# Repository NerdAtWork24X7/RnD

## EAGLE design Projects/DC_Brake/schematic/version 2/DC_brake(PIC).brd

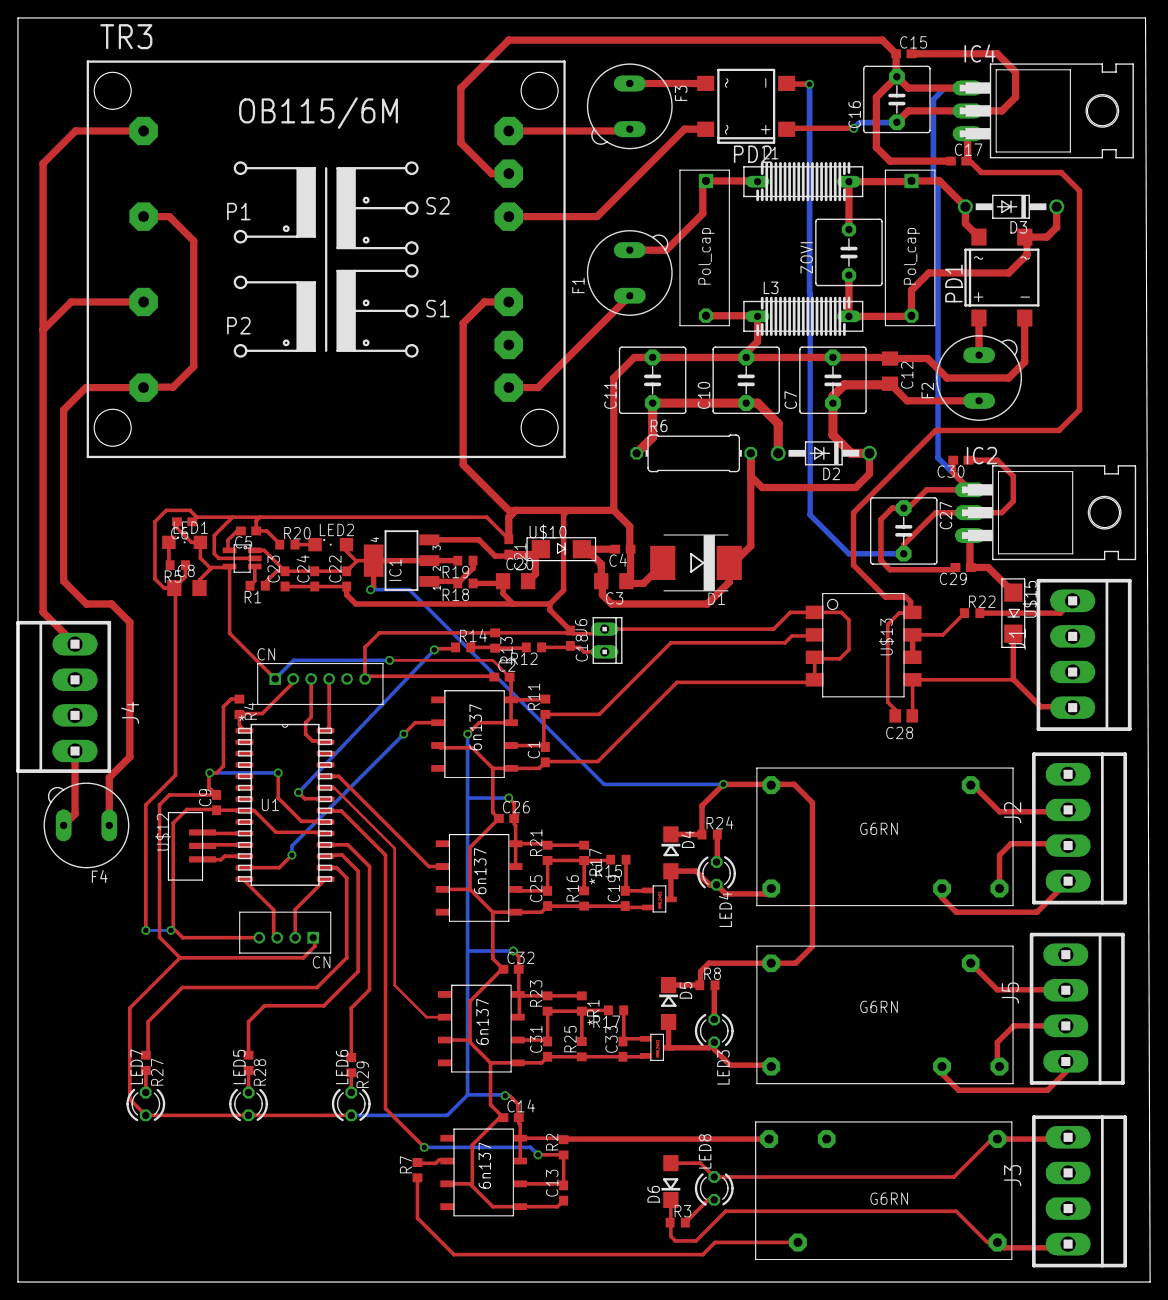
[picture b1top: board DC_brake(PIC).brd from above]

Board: 2 copper layers, 126.0 x 140.6 mm, 113 parts (0 on the bottom side), 71 nets.

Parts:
*R1, *R17: 100; R0603
C1, C13, C18, C19, C25, C31, C33: C0603
C2, C14, C26, C32: 0.1uF; C0603
C3, C8, C12: 10uF/16V; C1206
C4, C15, C30: 100nF MRa; C0603
C5: 1nF MRA; C0603
C6: 1uF/10V; C0603
C7: 4700uF/50V; C050-075X075
C9: 100nF/10V; C0603
C10, C11, C16, C27: 4700uF/50v; C050-075X075
C17, C29: 10mF MRa; C0603
C20: 1uF/50V; C1206
C21: 100nF/50V; C0603
C22: 100nF; C0603
C23: 1uF; C0603
C24: 10nF; C0603
C28: C0805
D1: 18V; SMC
D2: 1N4004; DO41-10
D3: DO41-10
D4, D5, D6: DO214AC
F1, F2, F3, F4: 19560
IC1: 317EMP; SOT223
IC2: lm7905; TO220H
IC4: lm7812; TO220H
J1, J2, J3, J4, J5: 1X4MTA
J6: 10X02MTA
L1, L3: DS10
LED1, LED2: SML1206
LED3, LED4, LED5, LED6, LED7, LED8: LED3MM
PD1, PD2: DF01S; DBS
R1, R5, R20: 10K; R0603
R2, R3, R7, R8, R11, R12, R13, R14, R15, R16, R17, R21, R22, R23, R24, R25, R27, R28, R29: 100; R0603
R4: 300; R0603
R6: 0411/12
R18: 2K; R0603
R19: 470R; R0603
T1, T2: IRML2402
TR3: OB115/6M
U1: PIC16F886-X/SO; SOIC28-W_MC
U$1: MIC5205-5.YMS; SMD
U$2, U$3, U$11, U$14: 6N137
U$4: 6PIN
U$5, U$9, U$16: RELAY
U$6: 4PIN
U$7, U$8: POLY_CAP; POL_CAP
U$10, U$15: DIODE
U$12: 3PIN
U$13: HCPL-3120
ZOVI: C5B7.2

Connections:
+12V: C17.2, C28.2, IC4.3, U$13.8(VCC)
-5V: C28.1, J1.1, U$13.5(VEE), U$15.-
CONTACT_RELAY: U1.24, U$11.2
D_GND: C15.1, C16.2, C17.1, C27.1, C29.2, C30.2, IC2.1, IC4.1, TR3.9
ES1: U1.12, U$12.3
ES2: U1.10, U$12.1
ES_COM: U1.11, U$12.2
GND: C1.1, C2.1, C3.1, C4.1, C5.1, C6.1, C7.2, C8.1, C9.1, C10.2, C11.2, C12.1, C13.1, C14.1, C18.1, C19.1, C20.1, C21.1, C22.1, C23.1, C24.1, C25.1, C26.1, C31.1, C32.1, C33.1, D1.A, J6.2, L3.1, PD1.-, R5.1, R13.1, R16.1, R18.1, R20.1, R25.1, T1.2, T2.2, TR3.7, U1.8, U1.19, U$1.2, U$2.3, U$2.5, U$3.3, U$3.5, U$4.6, U$6.4, U$7.2, U$11.3, U$11.5, U$13.1(N/C), U$13.3(CA), U$13.4(N/C), U$14.3, U$14.5
I2C_SCL: U1.14, U$6.3
I2C_SDA: U1.15, U$6.2
IGBT_TRIG: U1.13, U$3.2
LED1: R27.1, U1.16
LED2: R28.1, U1.17
LED3: R29.1, U1.18
unnamed: C29.1, IC2.3, U$15.+
unnamed: C5.2, U$1.4
unnamed: F1.2, L1.1, U$7.1
unnamed: R1.2, U$1.3
unnamed: F4.1, TR3.2, TR3.4
unnamed: F1.1, TR3.5
unnamed: J4.1, TR3.1, TR3.3
unnamed: F4.2, J4.4
unnamed: J1.4, R22.2
unnamed: C10.1, C11.1, D2.A, R6.1
unnamed: F3.2, TR3.10
unnamed: J2.1, U$9.NC
unnamed: C3.2, C4.2, C7.1, C12.2, D1.C, D2.C, F2.1, R6.2, U$10.-
unnamed: LED1.C, R5.2
unnamed: D6.A, J3.4, LED8.K, U$5.C2
unnamed: LED8.A, R3.2
unnamed: R7.2, U$2.2
unnamed: R7.1, U$5.COM
unnamed: D6.C, J3.1, R3.1, U$5.C1
unnamed: D5.A, LED3.K, T2.3, U$16.C2
unnamed: LED3.A, R8.2
unnamed: J5.1, U$16.NC
unnamed: J5.2, U$16.NO
unnamed: J5.3, U$16.COM
unnamed: PD2.AC1, TR3.8
unnamed: D3.A, L1.2, PD1.AC1, U$8.1, ZOVI.2
unnamed: D3.C, L3.2, PD1.AC2, U$8.2, ZOVI.1
unnamed: F3.1, PD2.AC2
unnamed: J2.2, U$9.NO
unnamed: C1.2, R11.1, U$3.6, U$13.2(AN)
unnamed: C15.2, C16.1, IC4.2, PD2.+
unnamed: C18.2, J6.1, R12.1
unnamed: J2.3, U$9.COM
unnamed: F2.2, PD1.+
unnamed: R12.2, R13.2, R14.2
unnamed: C19.2, R15.1, T1.1
unnamed: D4.A, LED4.K, T1.3, U$9.C2
unnamed: C33.2, R17.1, T2.1
unnamed: *R17.2, C25.2, R15.2, R16.2, R21.1, U$11.6
unnamed: LED2.C, R20.2
unnamed: IC1.1, R18.2, R19.1
unnamed: C20.2, C21.2, IC1.3, U$10.+
unnamed: C27.2, C30.1, IC2.2, PD2.-
unnamed: R22.1, U$13.6(VO), U$13.7(VO)
unnamed: *R1.2, C31.2, R17.2, R23.1, R25.2, U$14.6
unnamed: LED4.A, R24.2
unnamed: LED7.K, R27.2
unnamed: LED5.K, R28.2
unnamed: LED6.K, R29.2
RST: R4.2, U1.1, U$4.2
RX: U1.28, U$4.4
SER_RES_RELAY: U1.23, U$14.2
S_CMD: C13.2, R2.1, U1.21, U$2.6
TEMP: R14.1, U1.22
TX: U1.27, U$4.3
VCC: *R1.1, *R17.1, C2.2, C6.2, C8.2, C9.2, C14.2, C26.2, C32.2, LED1.A, LED5.A, LED6.A, LED7.A, R2.2, R4.1, R11.2, R21.2, R23.2, U1.20, U$1.5, U$2.7, U$2.8, U$3.7, U$3.8, U$4.1, U$5.NO, U$6.1, U$11.7, U$11.8, U$14.7, U$14.8
VDD: C22.2, C23.2, C24.2, D4.C, D5.C, IC1.4, LED2.A, R1.1, R8.1, R19.2, R24.1, U$1.1, U$9.C1, U$16.C1

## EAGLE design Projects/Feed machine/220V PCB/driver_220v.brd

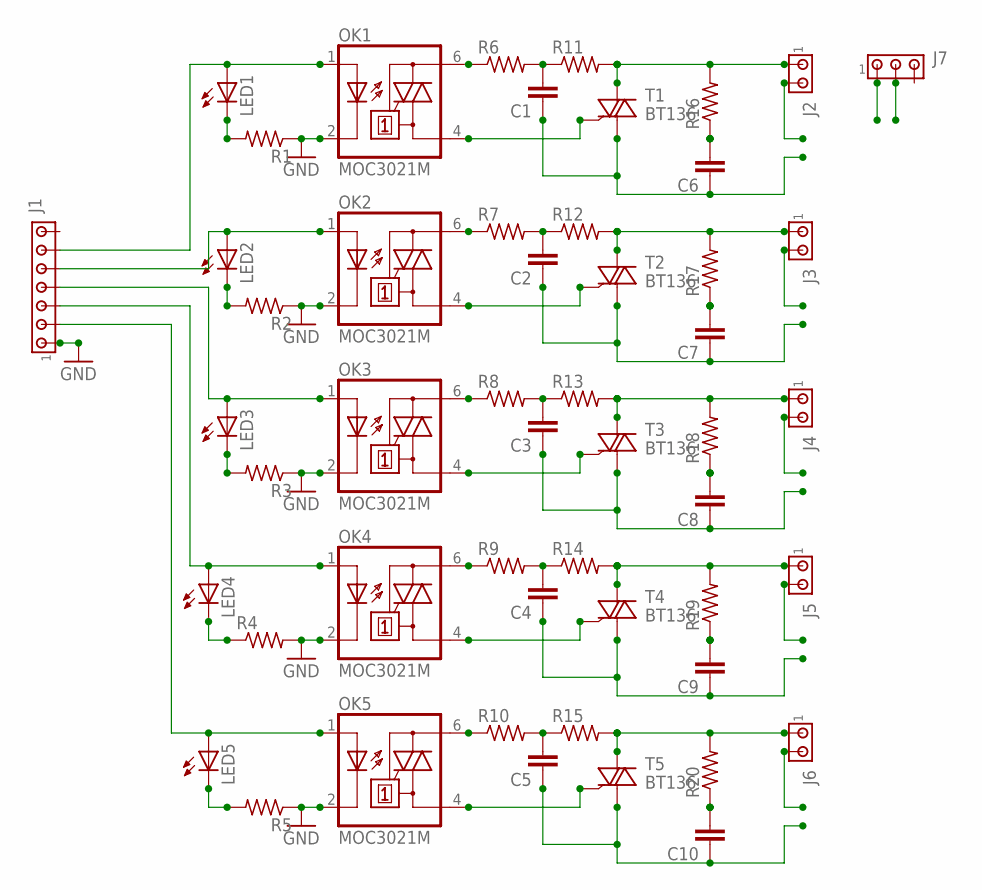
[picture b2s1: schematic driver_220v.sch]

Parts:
C1, C2, C3, C4, C5, C6, C7, C8, C9, C10: C2,5-3; C2.5-3
J1: MTA07-100; 10X07MTA
J2, J3, J4, J5, J6: MTA02-156; 1X2MTA
J7: MTA03-156; 1X3MTA
LED1, LED2, LED3, LED4, LED5: LED5MM
OK1, OK2, OK3, OK4, OK5: MOC3021M; DIL06
R1, R2, R3, R4, R5: R-US_R0603; R0603
R6, R7, R8, R9, R10, R11, R12, R13, R14, R15, R16, R17, R18, R19, R20: R-US_0207/10; 0207/10
T1, T2, T3, T4, T5: BT136; TO220AB

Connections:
GND: J1.1, OK1.2 (C), OK2.2 (C), OK3.2 (C), OK4.2 (C), OK5.2 (C), R1.1, R2.1, R3.1, R4.2, R5.1
LIVE: J2.2, J3.2, J4.2, J5.2, J6.2, J7.1
unnamed: OK2.6 (A2), R7.1
unnamed: C2.2, R7.2, R12.1
unnamed: J3.1, R12.2, R17.2, T2.2 (A2)
unnamed: OK2.4 (A1), T2.3 (G)
unnamed: C7.2, R17.1
unnamed: OK3.6 (A2), R8.1
unnamed: C3.2, R8.2, R13.1
unnamed: J4.1, R13.2, R18.2, T3.2 (A2)
unnamed: OK3.4 (A1), T3.3 (G)
unnamed: C8.2, R18.1
unnamed: OK4.6 (A2), R9.1
unnamed: C4.2, R9.2, R14.1
unnamed: J5.1, R14.2, R19.2, T4.2 (A2)
unnamed: OK4.4 (A1), T4.3 (G)
unnamed: C9.2, R19.1
unnamed: OK5.6 (A2), R10.1
unnamed: C5.2, R10.2, R15.1
unnamed: J6.1, R15.2, R20.2, T5.2 (A2)
unnamed: OK5.4 (A1), T5.3 (G)
unnamed: C10.2, R20.1
unnamed: J1.6, LED1.A, OK1.1 (A)
unnamed: J1.5, LED2.A, OK2.1 (A)
unnamed: OK1.6 (A2), R6.1
unnamed: C1.2, R6.2, R11.1
unnamed: J2.1, R11.2, R16.2, T1.2 (A2)
unnamed: OK1.4 (A1), T1.3 (G)
unnamed: J1.4, LED3.A, OK3.1 (A)
unnamed: C6.2, R16.1
unnamed: J1.3, LED4.A, OK4.1 (A)
unnamed: J1.2, LED5.A, OK5.1 (A)
unnamed: LED5.K (C), R5.2
unnamed: LED4.K (C), R4.1
unnamed: LED3.K (C), R3.2
unnamed: LED2.K (C), R2.2
unnamed: LED1.K (C), R1.2
NEUTRAL: C1.1, C2.1, C3.1, C4.1, C5.1, C6.1, C7.1, C8.1, C9.1, C10.1, J7.2, T1.1 (A1), T2.1 (A1), T3.1 (A1), T4.1 (A1), T5.1 (A1)

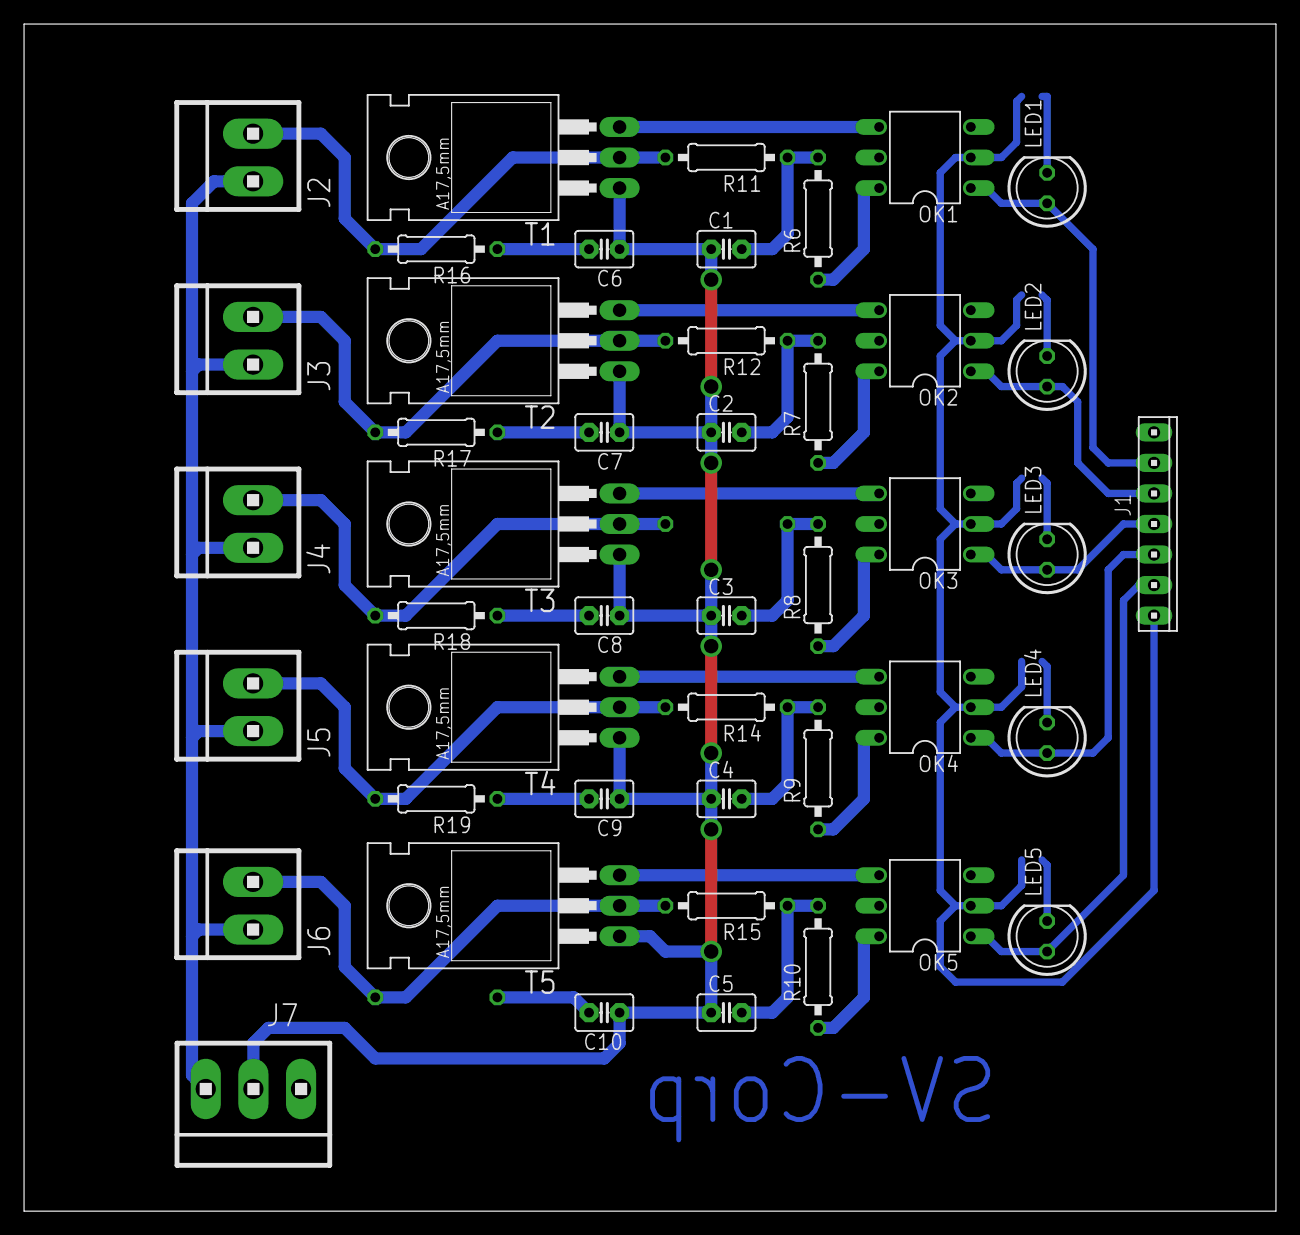
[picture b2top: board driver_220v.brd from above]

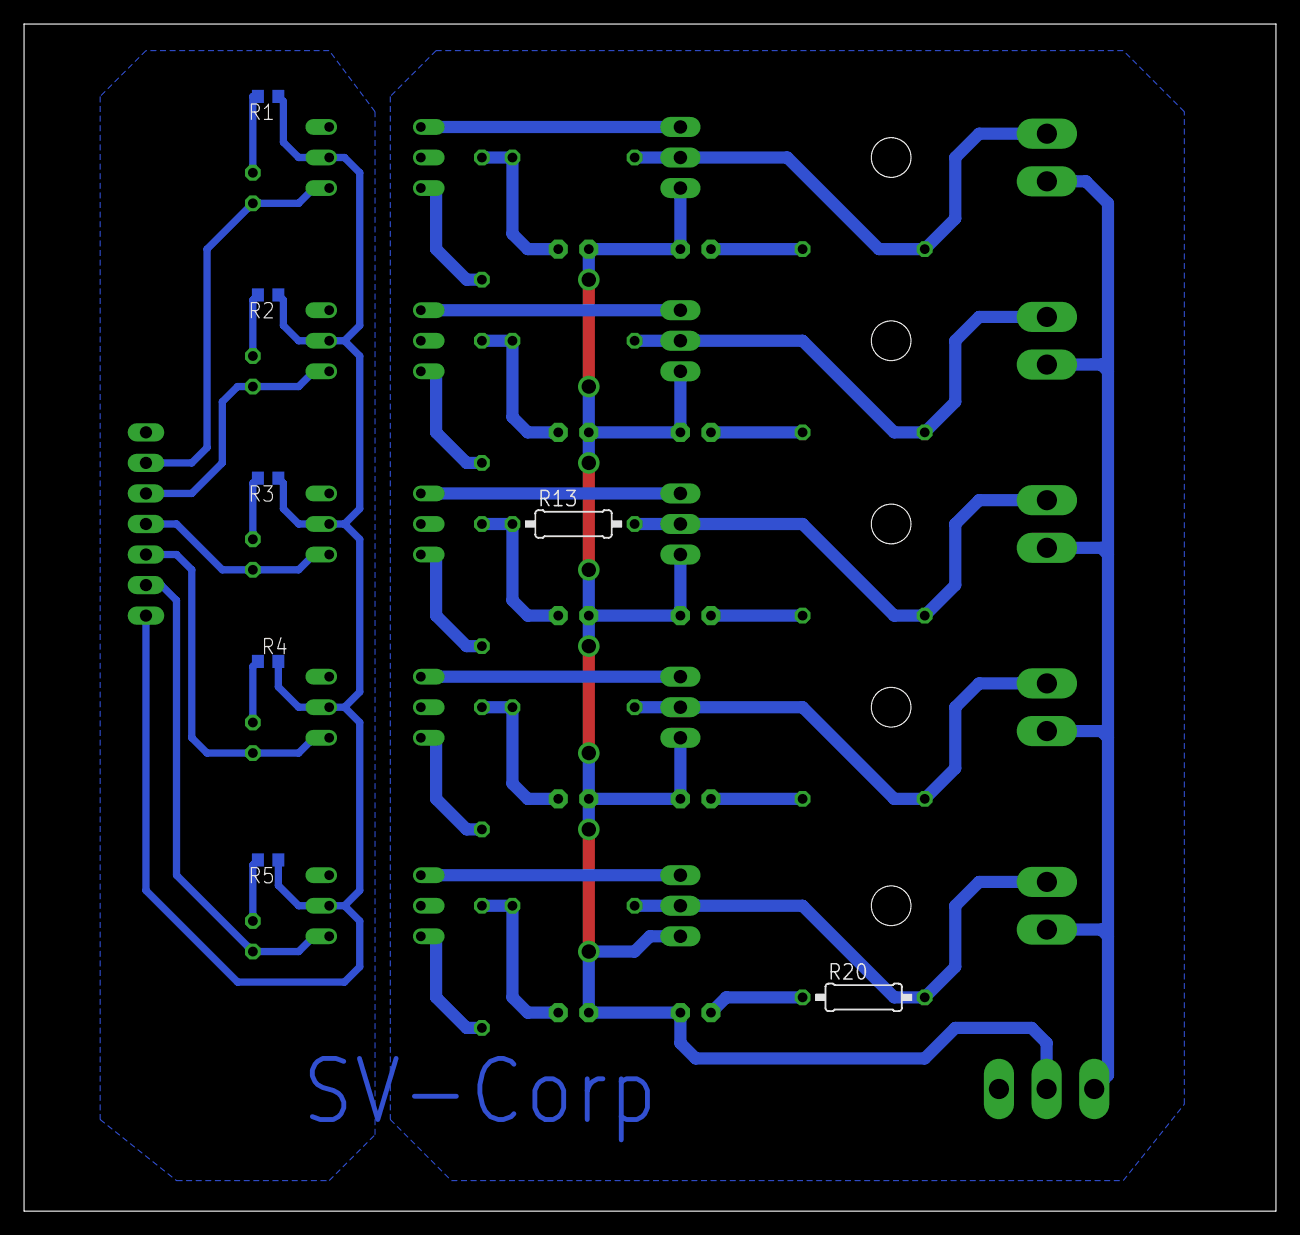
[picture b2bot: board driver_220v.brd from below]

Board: 2 copper layers, 104.1 x 98.7 mm, 52 parts (7 on the bottom side), 38 nets.

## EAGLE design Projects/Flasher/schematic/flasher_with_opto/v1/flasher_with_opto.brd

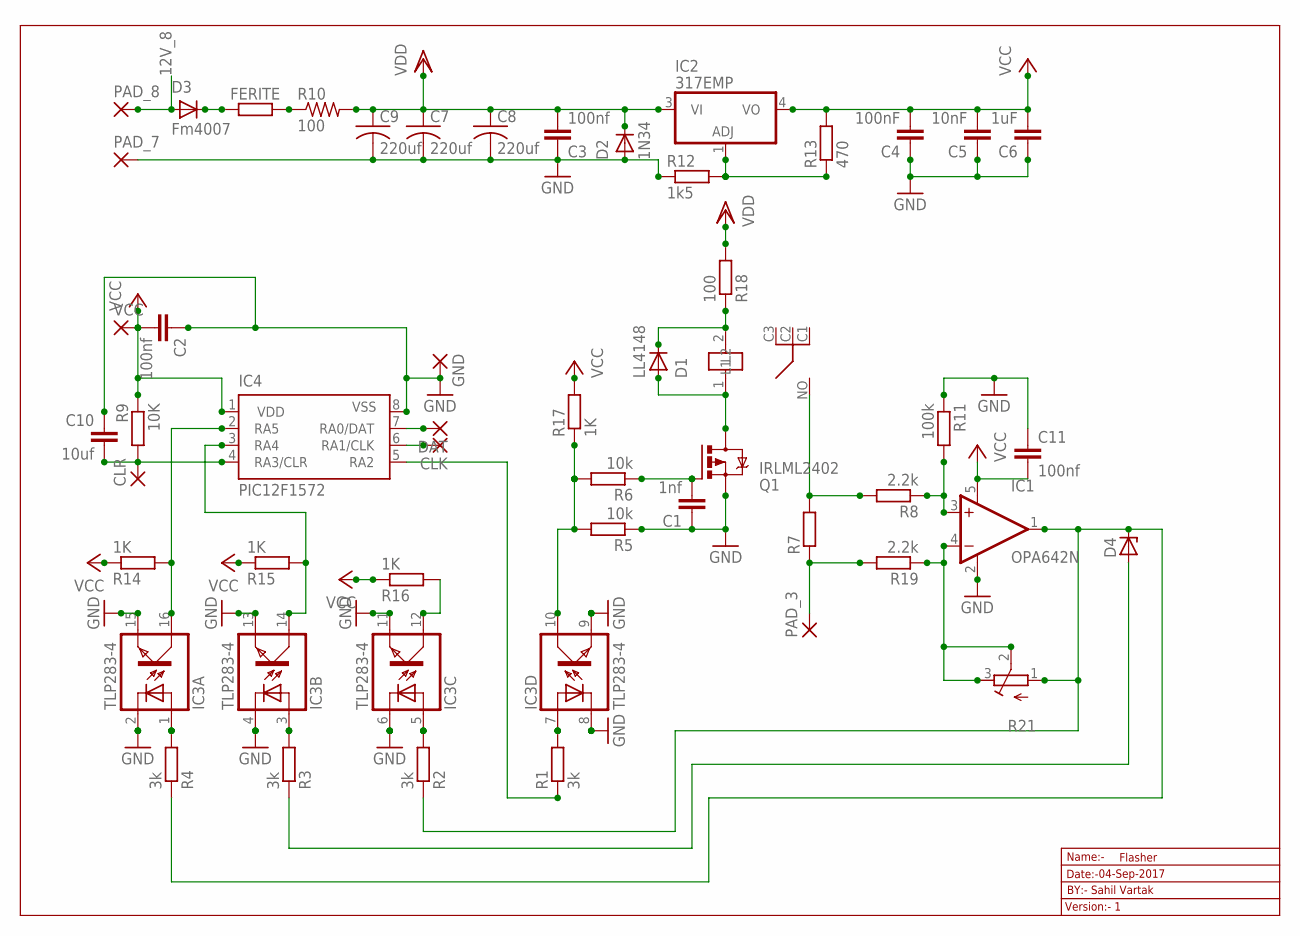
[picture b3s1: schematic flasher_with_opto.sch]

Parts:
C1: 1nf; C0603
C2, C3, C11: 100nf; C0603
C4: 100nF; C0603
C5: 10nF; C0603
C6: 1uF; C0603
C7, C8, C9: 220uf; C025-025X050
C10: 10uf; C0603
CLK: 1,6/0,8
CLR: 1,6/0,8
D1: LL4148; SMA-DO214AC
D2: 1N34; SMA-DO214AC
D3: Fm4007; SMA-DO214AC
D4: ZENER-DIODESOD80C; SOD80C
DAT: 1,6/0,8
FERITE: R-EU_R0603; R0603
GND: 1,6/0,8
IC1: OPA642N; SOT23-5
IC2: 317EMP; SOT223
IC3: TLP283-4; MINI-FLAT-16
IC4: PIC12F1572; SO-08
K2: RL703
PAD_3, PAD_7, PAD_8: 2,54/1,1
Q1: IRLML2402; MICRO3
R1, R2, R3, R4: 3k; R0603
R5, R6: 10k; R0603
R7: R-EU_VTA54; VTA54
R8, R19: 2.2k; R0603
R9: 10K; R0603
R10: 100; WSC2515
R11: 100k; R0603
R12: 1k5; R0603
R13: 470; R0603
R14, R15, R16, R17: 1K; R0603
R18: 100; R0603
R21: R-TRIMMTS63X; RTRIMTS63X
VCC: 1,6/0,8

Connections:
12V_8: D3.A, PAD_8.1
GND: C1.1, C2.1, C3.1, C4.1, C5.1, C6.1, C7.2, C8.2, C9.2, C10.1, C11.1, D2.A, GND.1, IC1.2 (V-), IC3.2 (C), IC3.4 (C), IC3.6 (C), IC3.8 (C), IC3.9 (EMIT), IC3.11 (EMIT), IC3.13 (EMIT), IC3.15 (EMIT), IC4.8 (VSS), PAD_7.1, Q1.2 (S), R5.1, R11.1, R12.1
unnamed: IC3.10 (COL), R5.2, R6.2, R17.1
unnamed: D1.A, K2.1 (L2), Q1.3 (D)
unnamed: D3.K (C), FERITE.1
unnamed: DAT.1, IC4.7 (RA0/DAT)
unnamed: CLK.1, IC4.6 (RA1/CLK)
unnamed: D1.K (C), K2.2 (L1), R18.1
unnamed: IC2.1 (ADJ), R12.2, R13.1
unnamed: FERITE.2, R10.1
unnamed: K2.NO, R7.2, R8.2
unnamed: IC3.12 (COL), R16.2
unnamed: IC4.5 (RA2), R1.1
unnamed: PAD_3.1, R7.1, R19.2
unnamed: IC3.14 (COL), IC4.3 (RA4), R15.2
unnamed: IC1.4 (-IN), R19.1, R21.2 (S), R21.3 (E)
unnamed: IC1.3 (+IN), R8.1, R11.2
unnamed: D4.C, IC1.1 (OUT), R2.1, R4.1, R21.1 (A)
unnamed: D4.A, R3.1
unnamed: C1.2, Q1.1 (G), R6.1
unnamed: IC3.1 (A), R4.2
unnamed: IC3.3 (A), R3.2
unnamed: IC3.5 (A), R2.2
unnamed: IC3.7 (A), R1.2
unnamed: IC3.16 (COL), IC4.2 (RA5), R14.2
unnamed: C10.2, CLR.1, IC4.4 (RA3/CLR), R9.2
VCC: C2.2, C4.2, C5.2, C6.2, C11.2, IC1.5 (V+), IC2.4 (VO), IC4.1 (VDD), R9.1, R13.2, R14.1, R15.1, R16.1, R17.2, VCC.1
VDD: C3.2, C7.1, C8.1, C9.1, D2.K (C), IC2.3 (VI), R10.2, R18.2

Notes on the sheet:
Name:-
Version:- 1
Date:-
Flasher
BY:- Sahil Vartak
04-Sep-2017

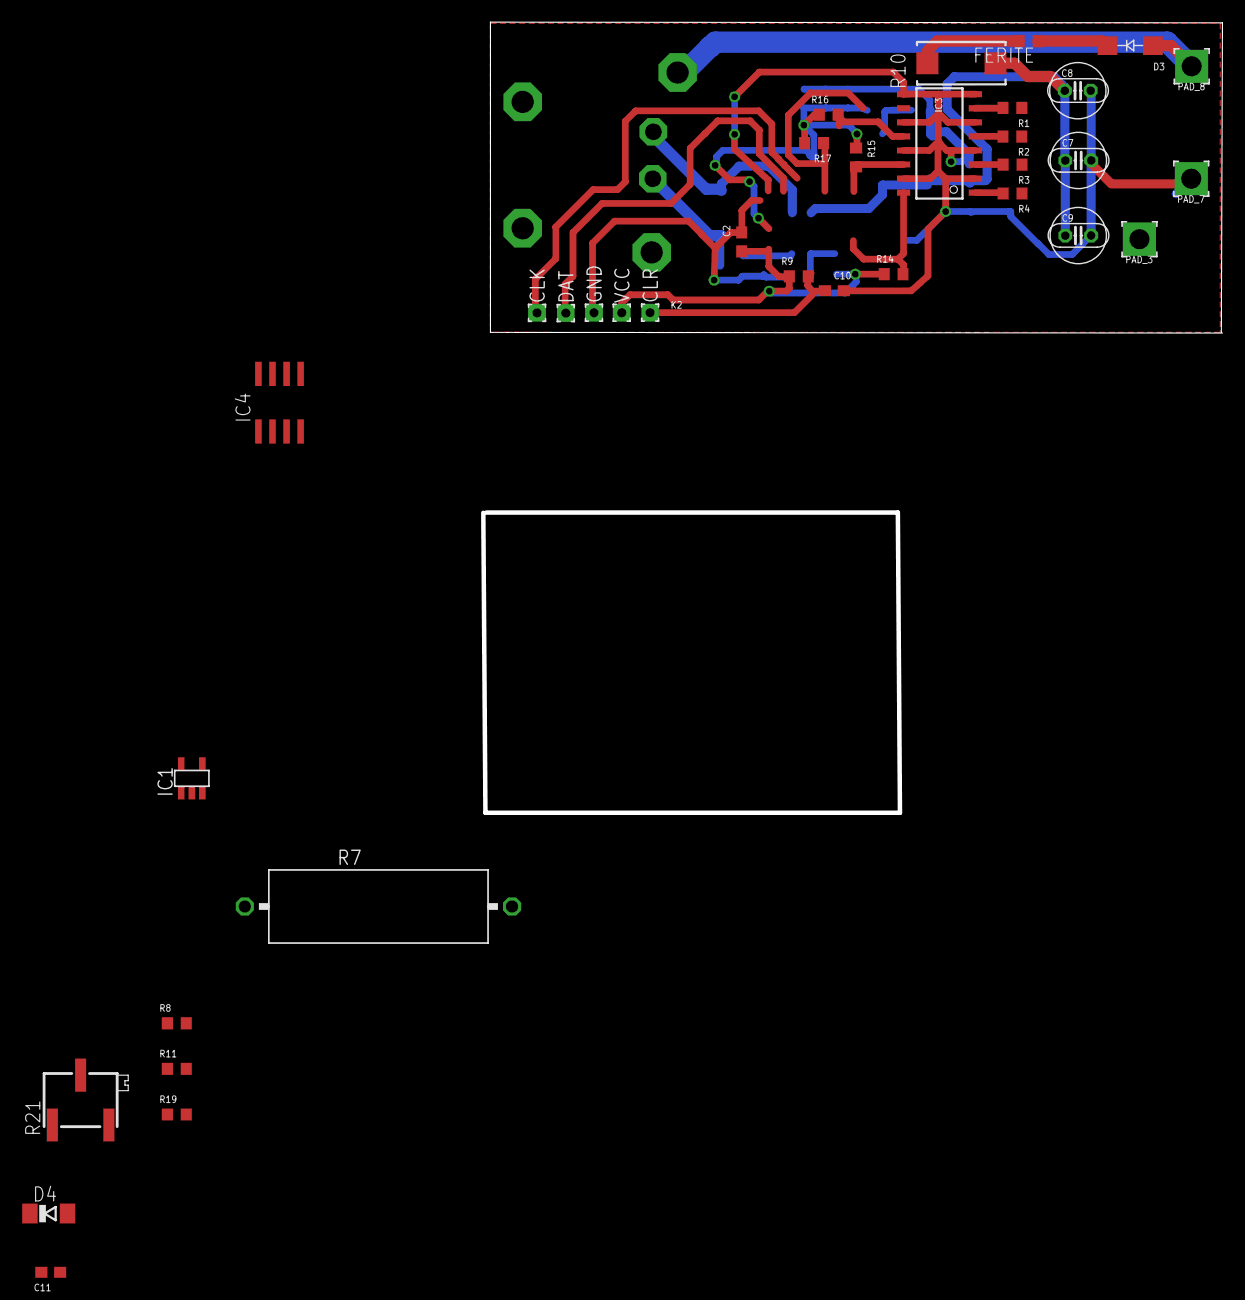
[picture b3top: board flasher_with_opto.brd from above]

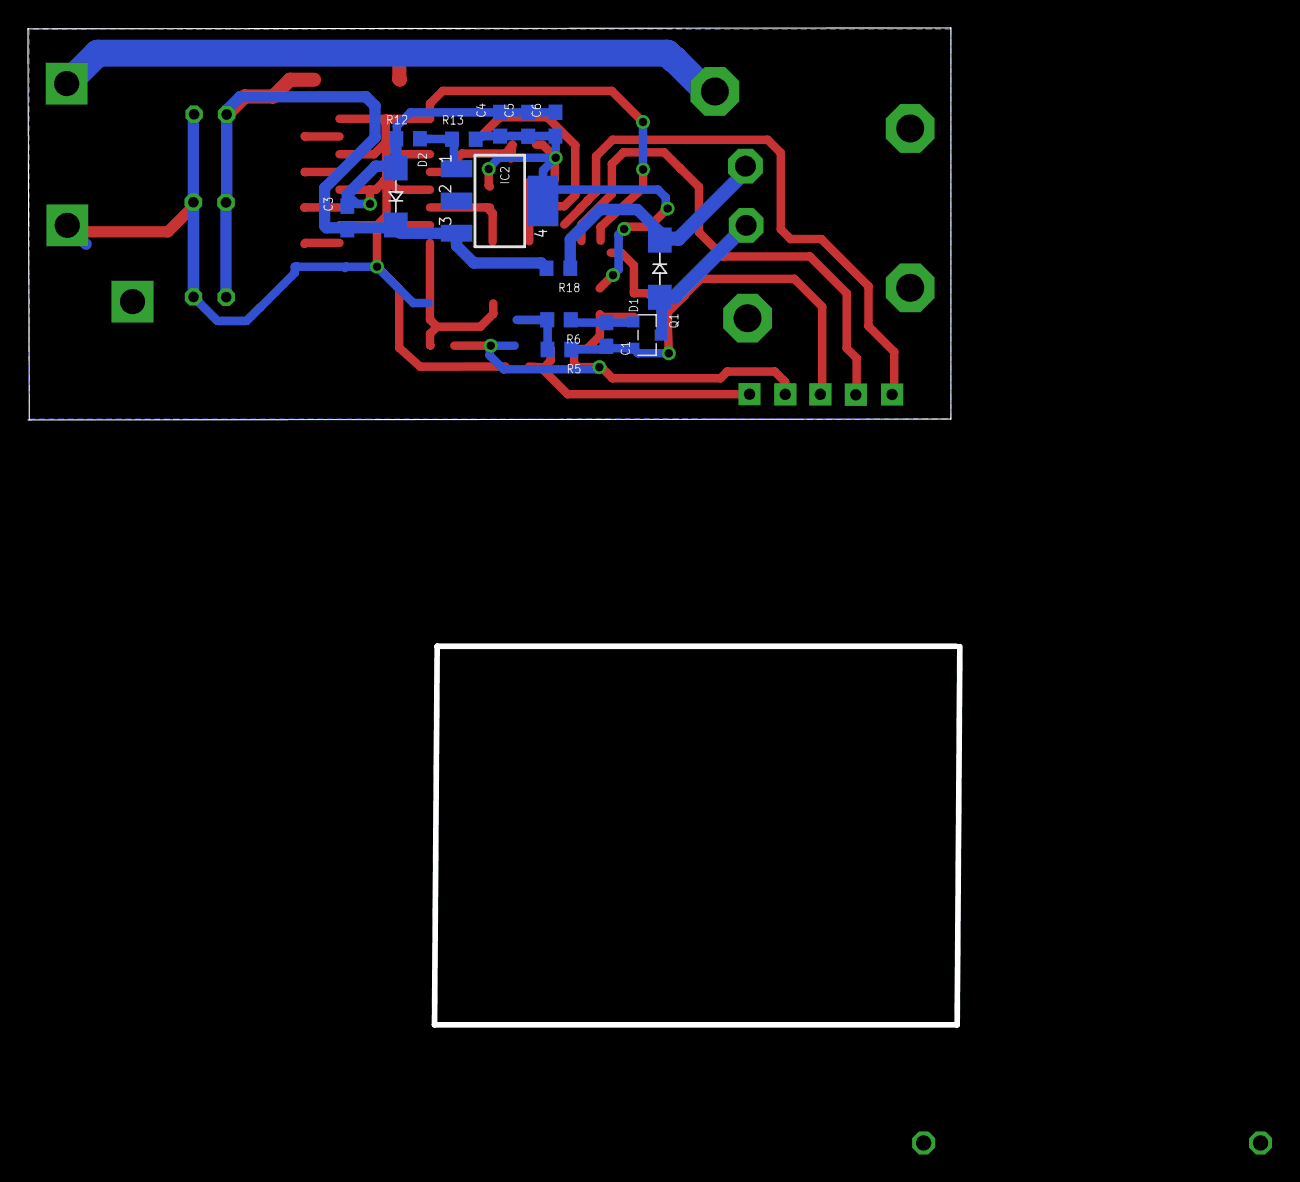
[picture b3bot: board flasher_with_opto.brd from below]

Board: 2 copper layers, 66.1 x 28.1 mm, 50 parts (15 on the bottom side), 28 nets.

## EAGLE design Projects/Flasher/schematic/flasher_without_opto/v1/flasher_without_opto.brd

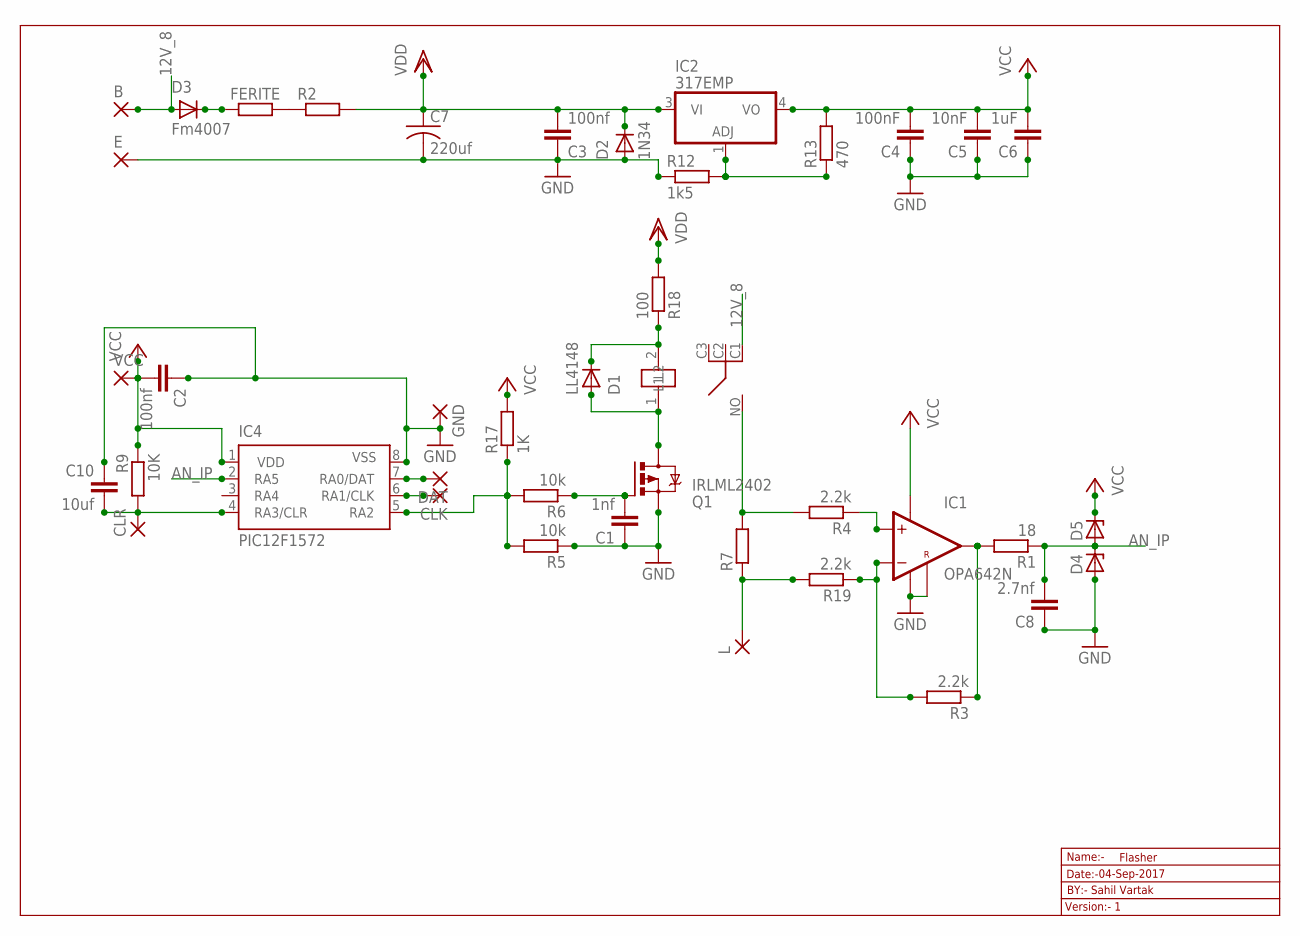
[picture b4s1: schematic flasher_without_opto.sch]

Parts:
B: 2,54/1,1
C1: 1nf; C0603
C2, C3: 100nf; C0603
C4: 100nF; C0603
C5: 10nF; C0603
C6: 1uF; C0603
C7: 220uf; C025-025X050
C8: 2.7nf; C0603
C10: 10uf; C0603
CLK: 1,6/0,8
CLR: 1,6/0,8
D1: LL4148; SMA-DO214AC
D2: 1N34; SMA-DO214AC
D3: Fm4007; SMA-DO214AC
D4, D5: ZENER-DIODESOD80C; SOD80C
DAT: 1,6/0,8
E: 2,54/1,1
FERITE: R-EU_R0603; R0603
GND: 1,6/0,8
IC1: OPA642N; INA181
IC2: 317EMP; SOT223
IC4: PIC12F1572; SO-08
K2: RL703
L: 2,54/1,1
Q1: IRLML2402; MICRO3
R1: 18; R0603
R2: RR5025; R5025
R3, R4, R19: 2.2k; R0603
R5, R6: 10k; R0603
R7: R-EU_0207/15; 0207/15
R9: 10K; R0603
R12: 1k5; R0603
R13: 470; R0603
R17: 1K; R0603
R18: 100; R0603
VCC: 1,6/0,8

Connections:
12V_8: B.1, D3.A, K2.C1
AN_IP: C8.2, D4.C, D5.A, IC4.2 (RA5), R1.1
GND: C1.1, C2.1, C3.1, C4.1, C5.1, C6.1, C7.2, C8.1, C10.1, D2.A, D4.A, E.1, GND.1, IC1.P$2 (V-), IC1.P$5 (REF), IC4.8 (VSS), Q1.2 (S), R5.1, R12.1
unnamed: FERITE.2, R2.1
unnamed: IC4.5 (RA2), R5.2, R6.2, R17.1
unnamed: D1.A, K2.1 (L2), Q1.3 (D)
unnamed: D3.K (C), FERITE.1
unnamed: DAT.1, IC4.7 (RA0/DAT)
unnamed: CLK.1, IC4.6 (RA1/CLK)
unnamed: D1.K (C), K2.2 (L1), R18.1
unnamed: IC2.1 (ADJ), R12.2, R13.1
unnamed: K2.NO, R4.2, R7.2
unnamed: L.1, R7.1, R19.2
unnamed: IC1.P$4 (-IN), R3.2, R19.1
unnamed: IC1.P$3 (+IN), R4.1
unnamed: IC1.P$1 (OUT), R1.2, R3.1
unnamed: C1.2, Q1.1 (G), R6.1
unnamed: C10.2, CLR.1, IC4.4 (RA3/CLR), R9.2
VCC: C2.2, C4.2, C5.2, C6.2, D5.C, IC1.P$6 (V+), IC2.4 (VO), IC4.1 (VDD), R9.1, R13.2, R17.2, VCC.1
VDD: C3.2, C7.1, D2.K (C), IC2.3 (VI), R2.2, R18.2

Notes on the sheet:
Name:-
Version:- 1
Date:-
Flasher
BY:- Sahil Vartak
04-Sep-2017

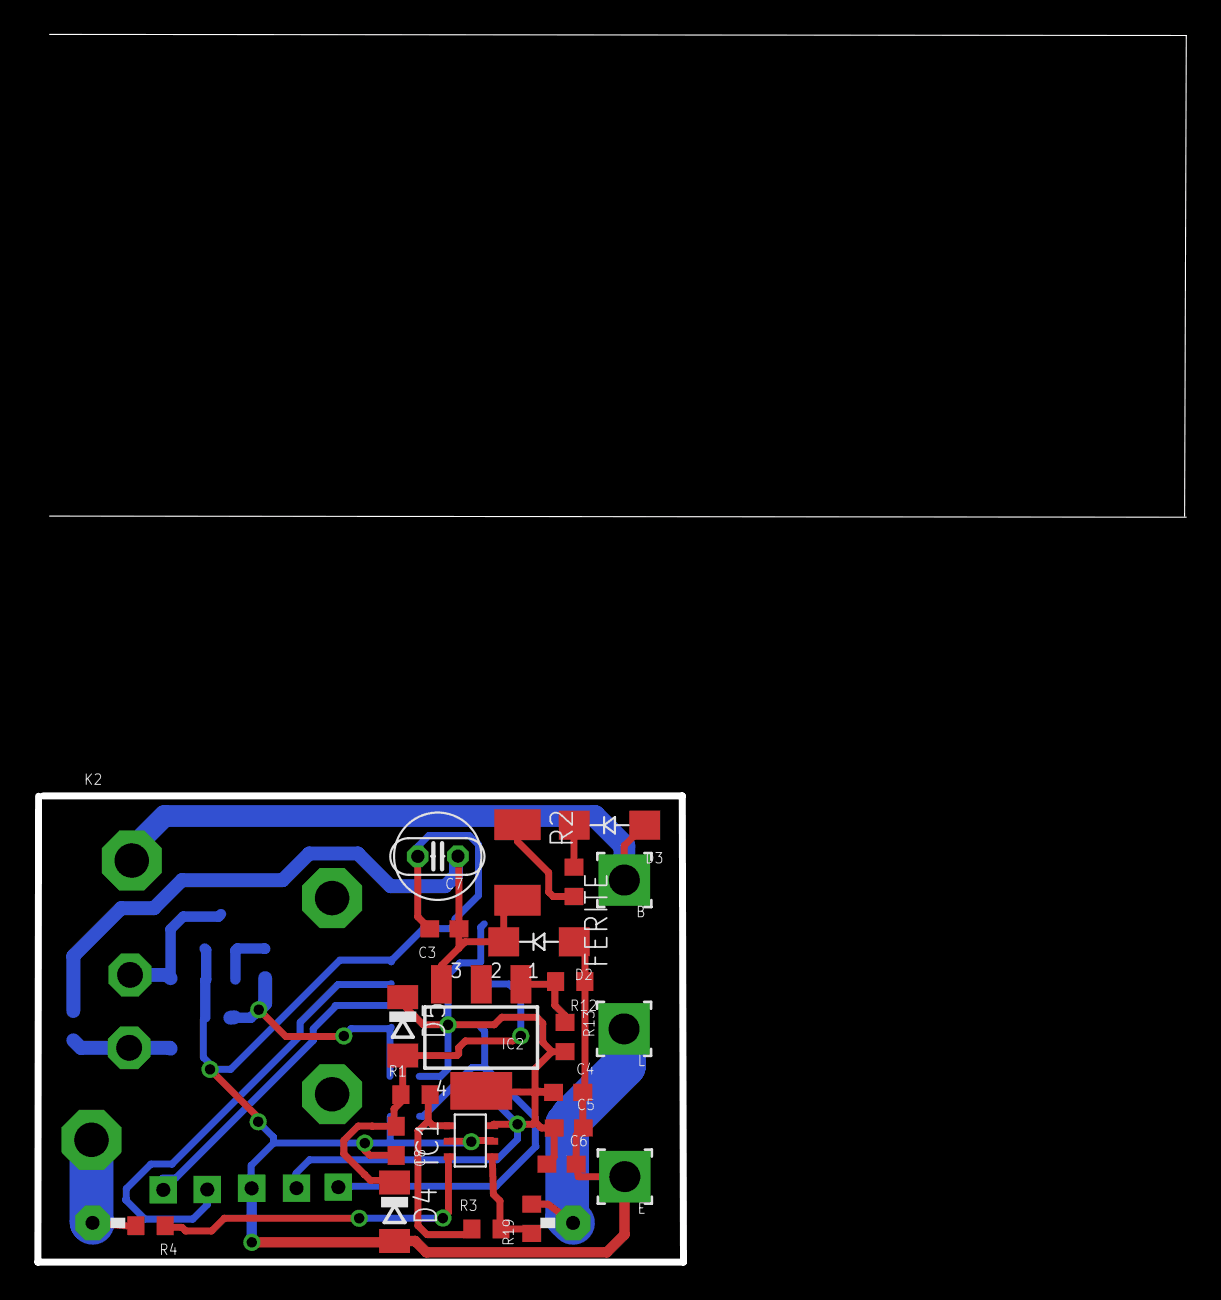
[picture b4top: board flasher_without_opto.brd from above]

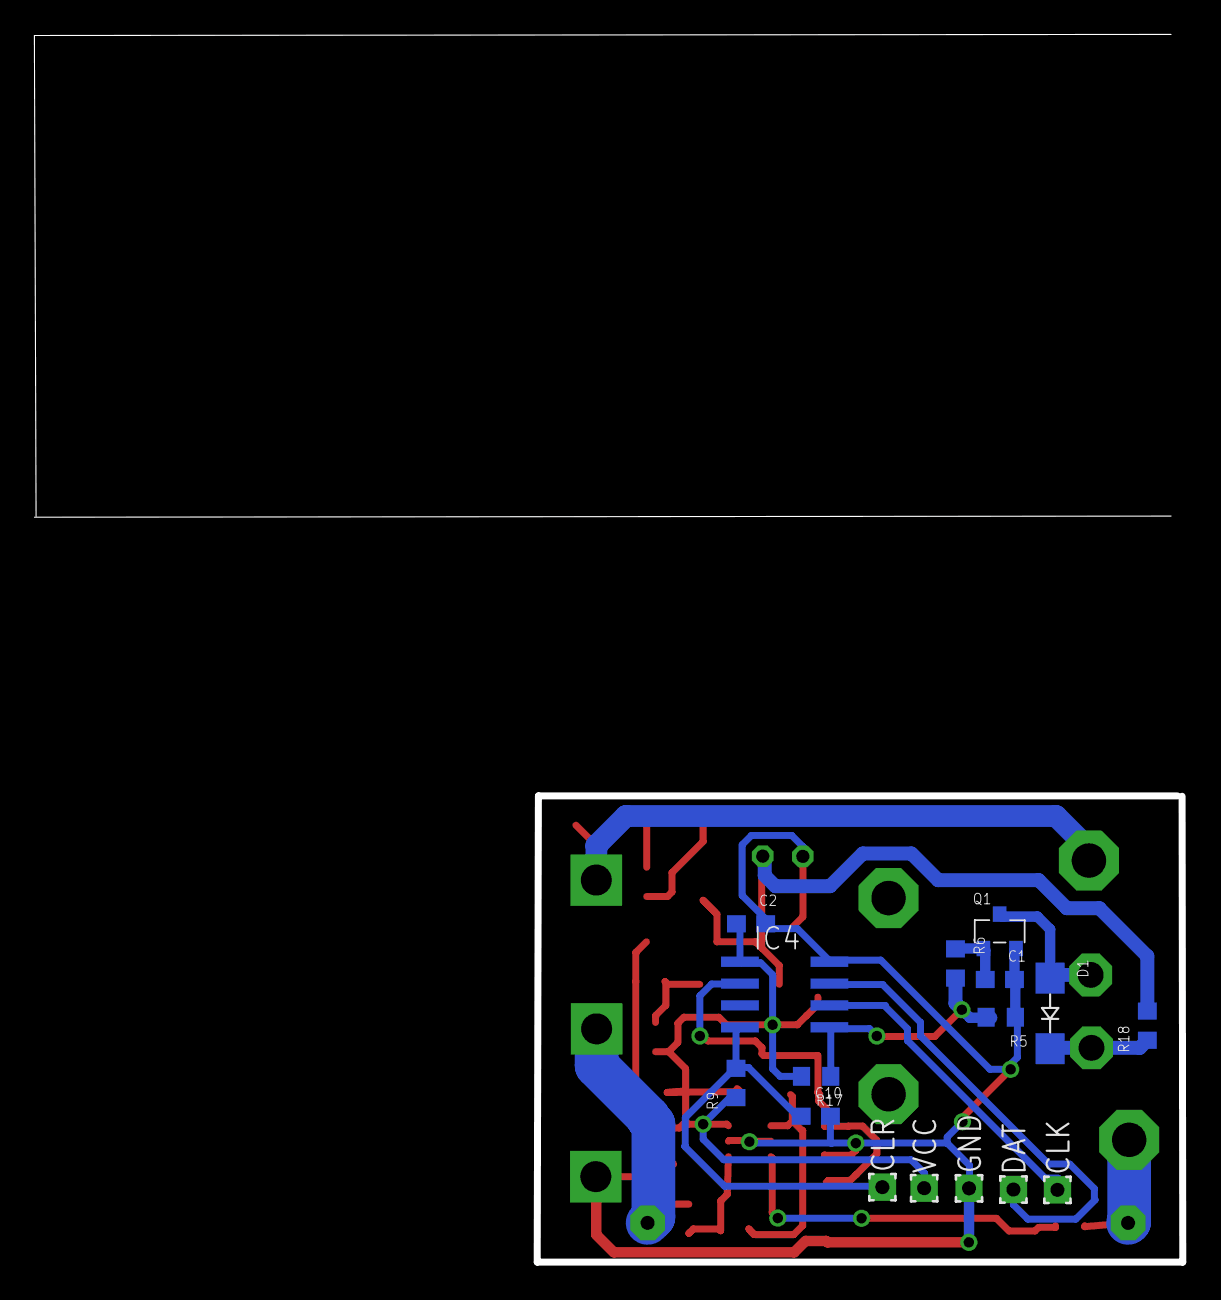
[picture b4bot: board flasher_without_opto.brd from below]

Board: 2 copper layers, 66.8 x 71.4 mm, 41 parts (17 on the bottom side), 20 nets.

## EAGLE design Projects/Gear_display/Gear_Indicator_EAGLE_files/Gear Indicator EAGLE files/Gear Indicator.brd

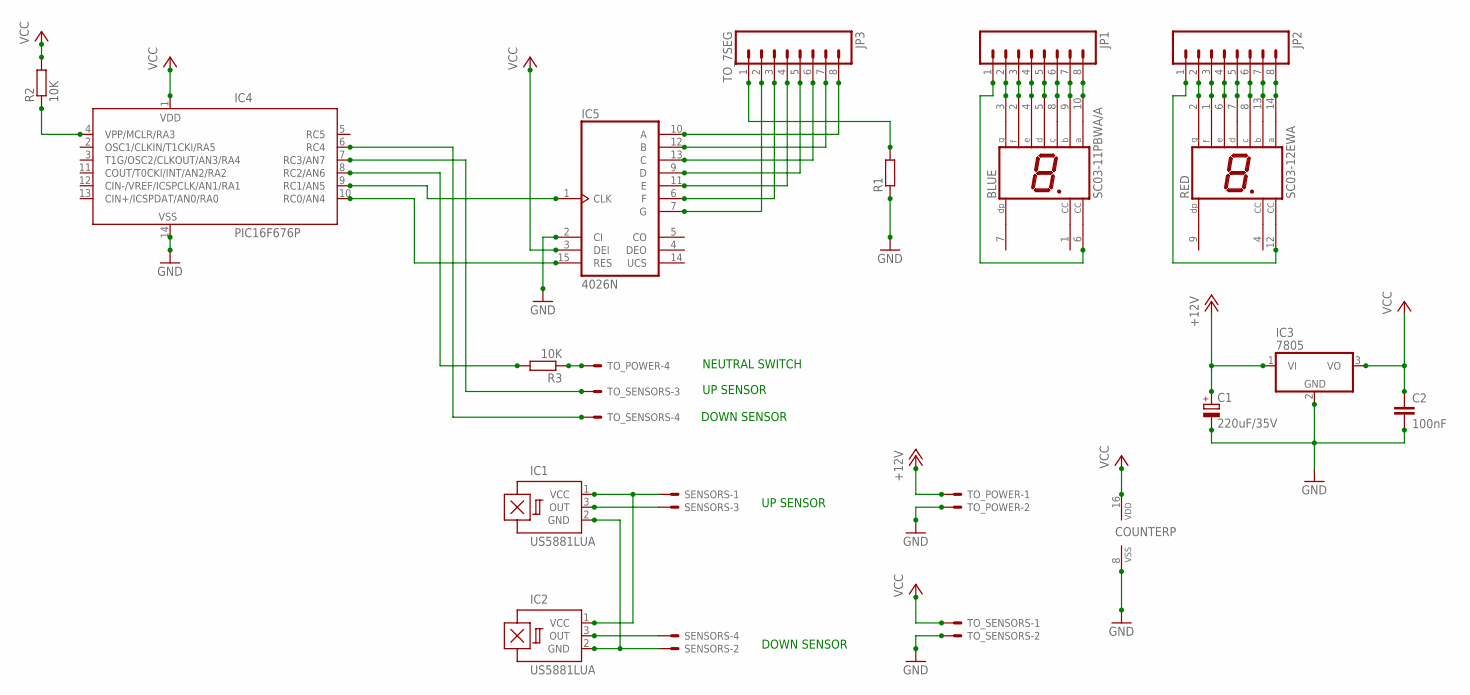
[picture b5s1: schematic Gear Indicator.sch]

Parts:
BLUE: SC03-11PBWA/A; 0.3A
C1: 220uF/35V; E2,5-6
C2: 100nF; C050-030X075
COUNTER: 4026; TSSOP16
IC1, IC2: US5881LUA; SIP3-UA
IC3: 7805; TO220V
IC4: PIC16F676P; DIL14
IC5: 4026N; DIL16
JP1, JP2: M08; 1X08
JP3: TO_7SEG; 1X08
R1: R-EU_0309/12; 0309/12
R2, R3: 10K; 0207/10
RED: SC03-12EWA; 0.3B
SENSORS: 22-05-7048-04; 7395-04
TO_POWER: 22-05-7048-04; 7395-04
TO_SENSORS: 22-05-7048-04; 7395-04

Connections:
+12V: C1.+, IC3.1 (VI), TO_POWER.1
A: IC5.10 (A), JP3.8
B: IC5.12 (B), JP3.7
BLUE_A: BLUE.10 (A), JP1.8
BLUE_B: BLUE.9 (B), JP1.7
BLUE_C: BLUE.8 (C), JP1.6
BLUE_CC: BLUE.6 (CC), JP1.1
BLUE_D: BLUE.5 (D), JP1.5
BLUE_E: BLUE.4 (E), JP1.4
BLUE_F: BLUE.2 (F), JP1.3
BLUE_G: BLUE.3 (G), JP1.2
C: IC5.13 (C), JP3.6
CC: JP3.1, R1.2
D: IC5.9 (D), JP3.5
DOWN: IC4.6 (RC4), TO_SENSORS.4
E: IC5.11 (E), JP3.4
F: IC5.6 (F), JP3.3
G: IC5.7 (G), JP3.2
GND: C1.-, C2.2, COUNTER.8 (VSS), IC3.2 (GND), IC4.14 (VSS), IC5.2 (CI), R1.1, TO_POWER.2, TO_SENSORS.2
unnamed: IC4.8 (RC2/AN6), R3.2
unnamed: IC4.9 (RC1/AN5), IC5.1 (CLK)
unnamed: R3.1, TO_POWER.4
unnamed: IC1.2 (GND), IC2.2 (GND), SENSORS.2
unnamed: IC1.1 (VCC), IC2.1 (VCC), SENSORS.1
unnamed: IC1.3 (OUT), SENSORS.3
unnamed: IC2.3 (OUT), SENSORS.4
RED_A: JP2.8, RED.14 (A)
RED_B: JP2.7, RED.13 (B)
RED_C: JP2.6, RED.8 (C)
RED_CC: JP2.1, RED.12 (CC)
RED_D: JP2.5, RED.7 (D)
RED_E: JP2.4, RED.6 (E)
RED_F: JP2.3, RED.1 (F)
RED_G: JP2.2, RED.2 (G)
RESET: IC4.4 (VPP/MCLR/RA3), R2.1
UP: IC4.7 (RC3/AN7), TO_SENSORS.3
VCC: C2.1, COUNTER.16 (VDD), IC3.3 (VO), IC4.1 (VDD), IC5.3 (DEI), R2.2, TO_SENSORS.1
VDD: IC5.16 (VDD)
VSS: IC5.8 (VSS)
ZERO: IC4.10 (RC0/AN4), IC5.15 (RES)

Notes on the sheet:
NEUTRAL SWITCH
UP SENSOR
DOWN SENSOR
